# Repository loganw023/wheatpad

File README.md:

# wheatpad
This is a macropad for personal use. It has six keys, a rotary encoder with a switch, and an OLED screen. I used KMK firmware to code the macropad. I used the macropad as an introduction to PCB design and to increase my CAD experience. 

## Build Photo

## CAD
I used Fusion360 to create my macropad case. There are two parts: a bottom and a top. In the physical model, the PCB will be moved up to allow enough space for keycaps to be pressed. 

## PCB
Schematic: 

PCB:

## Firmware
I updated the firmware for the finished product! 

## BOM
* 6x Cherry MX Switches
* 6x DSA Keycaps
* 4x M3x5x4 Heatset inserts
* 4x M3x16mm SHCS Bolts
* 1x 0.91" 128x32 OLED Display
* 1x EC11 Rotary Encoder
* 1x XIAO RP2040
* 1x Case (2 printed parts)
* 1x Custom PCB

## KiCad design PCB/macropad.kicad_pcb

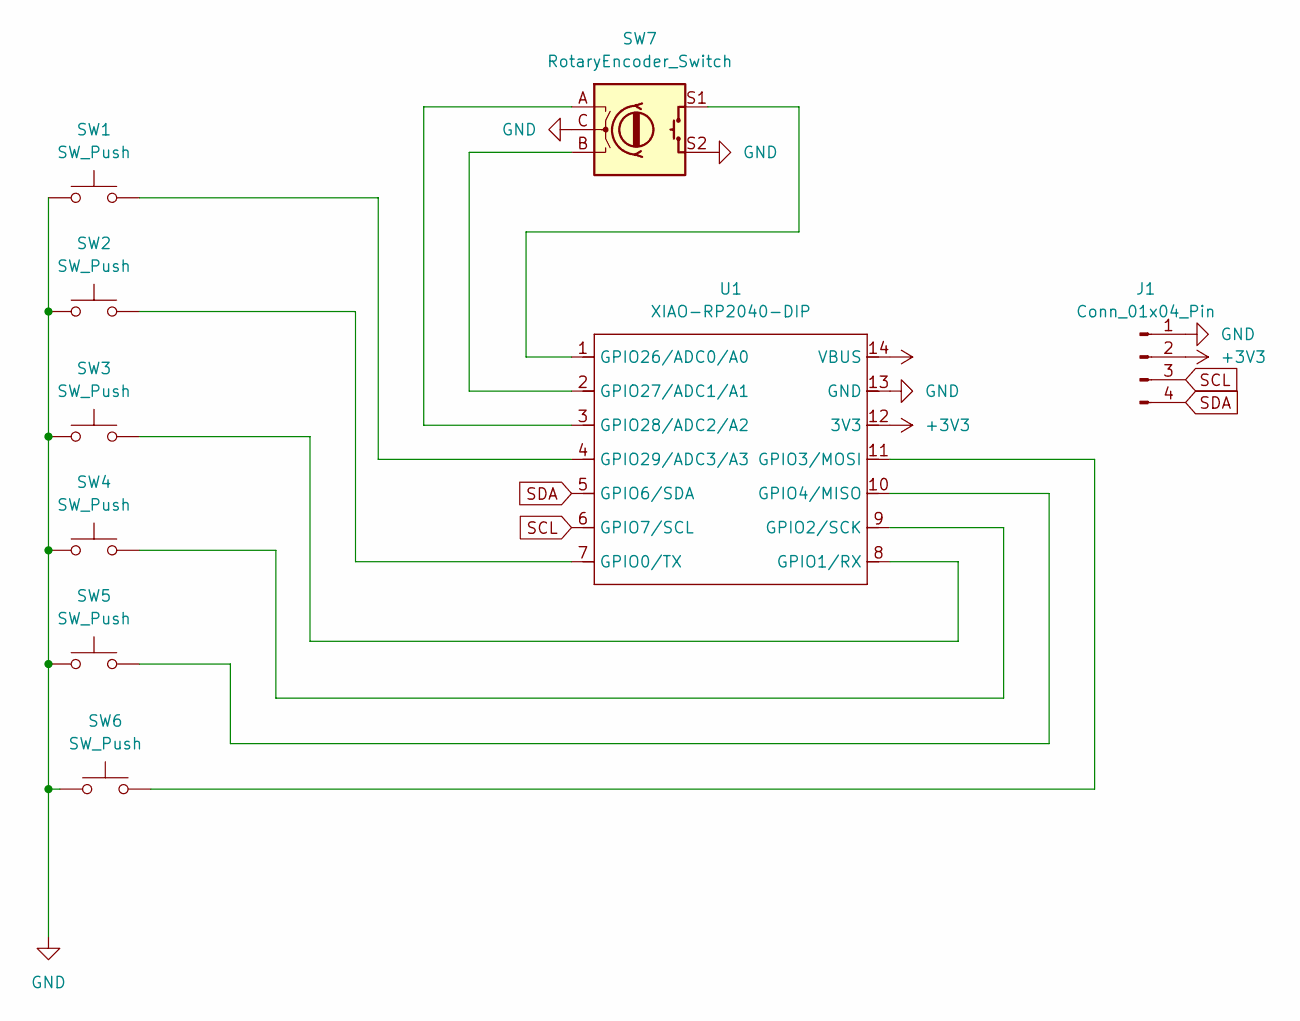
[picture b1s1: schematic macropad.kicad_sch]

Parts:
J1: Conn_01x04_Pin; SSD1306-0.91-OLED-4pin-128x32
SW1, SW2, SW3, SW4, SW5, SW6: SW_Push; SW_Cherry_MX_1.00u_PCB
SW7: RotaryEncoder_Switch; RotaryEncoder_Alps_EC11E-Switch_Vertical_H20mm
U1: XIAO-RP2040-DIP

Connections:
+3V3: J1.2, U1.12 (3V3)
+5V: U1.14 (VBUS)
GND: J1.1, SW1.1, SW2.1, SW3.1, SW4.1, SW5.1, SW6.1, SW7.C, SW7.S2, U1.13 (GND)
unnamed: SW2.2, U1.7 (GPIO0/TX)
unnamed: SW3.2, U1.8 (GPIO1/RX)
unnamed: SW4.2, U1.9 (GPIO2/SCK)
unnamed: SW6.2, U1.11 (GPIO3/MOSI)
unnamed: SW5.2, U1.10 (GPIO4/MISO)
unnamed: SW7.S1, U1.1 (GPIO26/ADC0/A0)
unnamed: SW7.B, U1.2 (GPIO27/ADC1/A1)
unnamed: SW7.A, U1.3 (GPIO28/ADC2/A2)
unnamed: SW1.2, U1.4 (GPIO29/ADC3/A3)
SCL: J1.3, U1.6 (GPIO7/SCL)
SDA: J1.4, U1.5 (GPIO6/SDA)

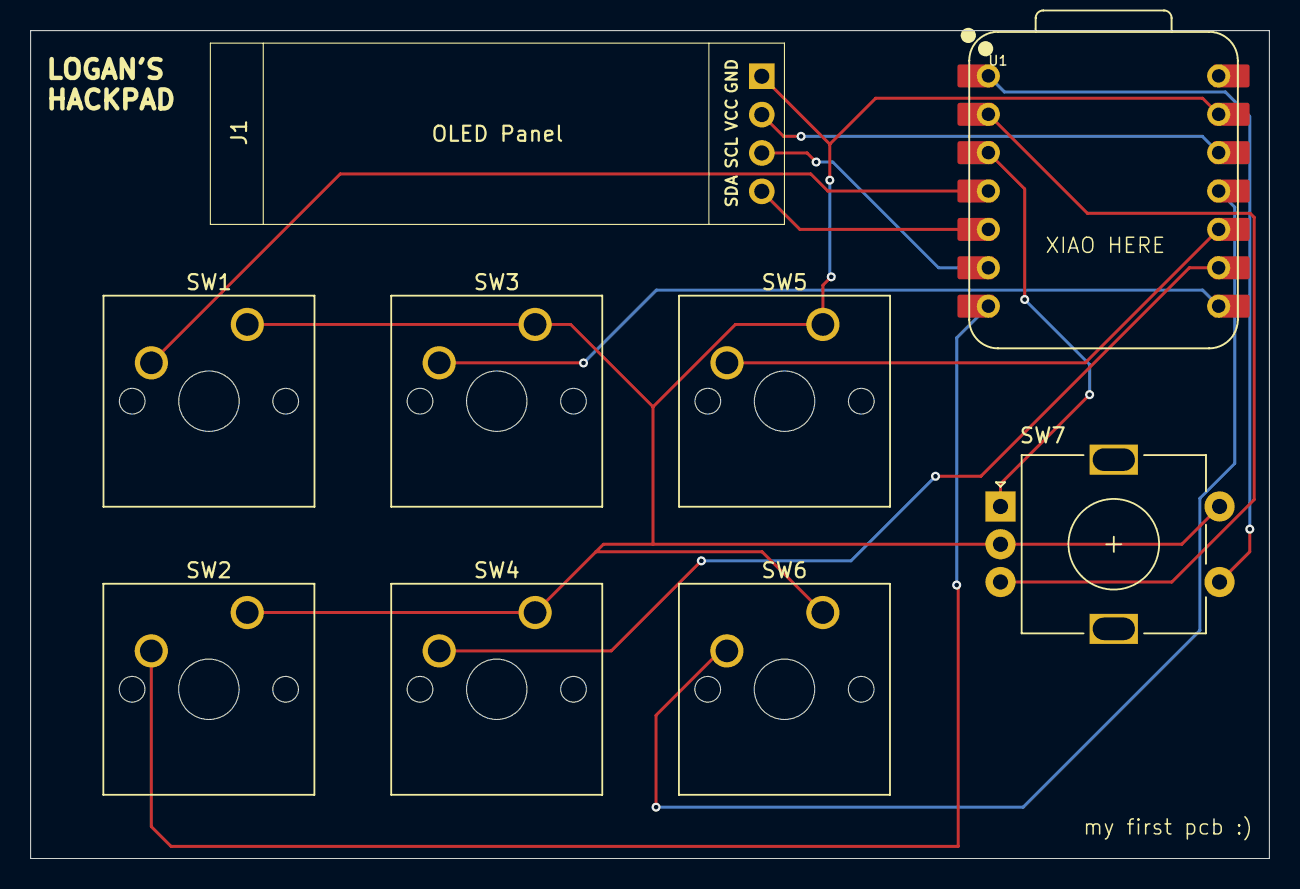
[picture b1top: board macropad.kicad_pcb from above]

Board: 2 copper layers, 82.0 x 54.8 mm, 9 parts (0 on the bottom side), 13 nets.

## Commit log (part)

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2025-07-02 adding my files
